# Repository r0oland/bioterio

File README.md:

# bioterio

Log and display temperature and humidity in your terrarium, aquarium, plant box or if you are totally crazy even your own room...

## Detailed Instructions

See https://www.laserhannes.de/ for details one day...

## Hardware

- D1 Mini
  - ESP8266 uC
  - [SPI and I²C pins for D1 Mini](https://steve.fi/hardware/d1-pins/)
- SH1106
  - 128X64 NONAME display
  - 1,3" OLED Display Weiß SH1106 128x64 SPI 7 Pin Modul Arduino Raspberry Pi
  - <https://www.ebay.de/itm/162572740754>
  - compatible to SSD1305???
- SHT21
  - Humidity and Temperature Sensor IC

## ESP Home

## Licence Infos

[Raleway Font by Google](https://fonts.google.com/specimen/Raleway#glyphs) under the [Open Font License](https://scripts.sil.org/cms/scripts/page.php?site_id=nrsi&id=OFL).

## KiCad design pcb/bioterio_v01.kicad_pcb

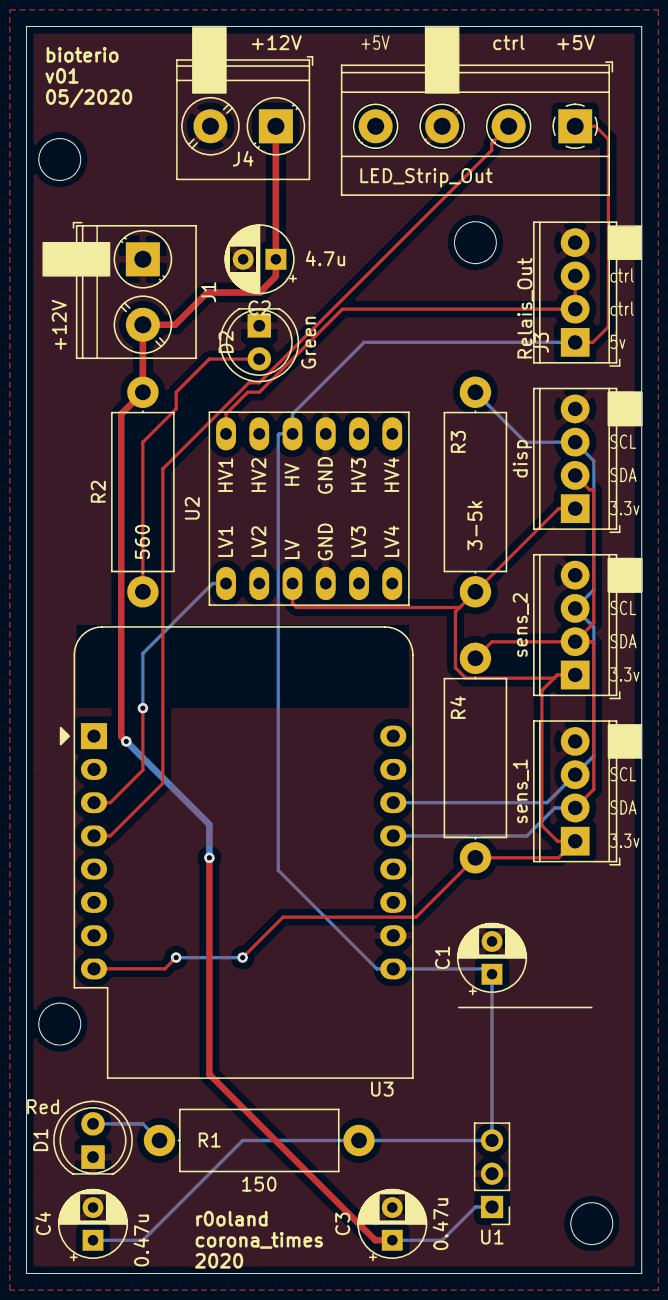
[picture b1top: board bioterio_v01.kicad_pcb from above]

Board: 2 copper layers, 47.0 x 95.2 mm, 20 parts (0 on the bottom side), 11 nets.

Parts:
C1, C2: 4.7u; CP_Radial_D5.0mm_P2.50mm
C3, C4: 0.47u; CP_Radial_D5.0mm_P2.50mm
D1: Red; LED_D5.0mm
D2: Green; LED_D5.0mm
J1, J4: +12V; TerminalBlock_Phoenix_PT-1,5-2-5.0-H_1x02_P5.00mm_Horizontal
J3: Relais_Out; TerminalBlock_Phoenix_MPT-0,5-4-2.54_1x04_P2.54mm_Horizontal
R1: 150; R_Axial_DIN0414_L11.9mm_D4.5mm_P15.24mm_Horizontal
R2: 560; R_Axial_DIN0414_L11.9mm_D4.5mm_P15.24mm_Horizontal
R3, R4: 3-5k; R_Axial_DIN0414_L11.9mm_D4.5mm_P15.24mm_Horizontal
U1: L7805; PinHeader_1x03_P2.54mm_Vertical
U2: voltage_conv
U3: WeMos_D1_mini; WEMOS_D1_mini_light
ctrl: LED_Strip_Out; TerminalBlock_Phoenix_MKDS-1,5-4-5.08_1x04_P5.08mm_Horizont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
disp: BME280_2; TerminalBlock_Phoenix_MPT-0,5-4-2.54_1x04_P2.54mm_Horizontal
sens_1: Disp_Out; TerminalBlock_Phoenix_MPT-0,5-4-2.54_1x04_P2.54mm_Horizontal
sens_2: BME280_1; TerminalBlock_Phoenix_MPT-0,5-4-2.54_1x04_P2.54mm_Horizontal

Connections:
+3V3: R3.1, R4.1, U2.3, U3.8, disp.1, sens_1.1, sens_2.1
+5V: C1.1, C4.1, J3.1, R1.2, U1.3, U2.10, U3.9, ctrl.1
+12V: C2.1, C3.1, J1.2, J4.1, R2.2, U1.1
GND: C1.2, C2.2, C3.2, C4.2, D1.1, D2.1, J1.1, J3.4, J4.2, U1.2, U2.4, U2.9, U3.10, ctrl.3, disp.4, sens_1.4, sens_2.4
I²C_SCL: R3.2, U3.14, disp.3, sens_1.3, sens_2.3
I²C_SDA: R4.2, U3.13, disp.2, sens_1.2, sens_2.2
unnamed: D1.2, R1.1
unnamed: D2.2, R2.1
RelaisCtrl3V: U2.1, U3.3
RelaisCtrl5V: J3.2, J3.3, U2.12
led_ctrl_d5: U3.4, ctrl.2

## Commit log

2020-05-02 moving code to own repo
2020-05-02 add firmware and pcb folders, move pcb files here as well
2020-05-02 removing adafruit example files
2020-05-03 playing with OLED display
2020-05-10 adding full schematic and PCB
2020-05-12 getting gerber and such
2020-05-31 updated pcb, slight firmware updates
2020-05-31 running median + better display output
2022-02-17 moving things around
2022-02-17 - basic stuff working but it aint pretty
2022-02-17 checking somthing
2022-03-13 - clean up and getting eps version up and running
2022-03-13 minor readme update
